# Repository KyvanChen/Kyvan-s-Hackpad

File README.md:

# Kyvan-s-Hackpad
This is my hackpad, I plan on using this for cadding in robotics. This is my first PCB and I followed hack club's tutorial sorta.

Hackpad PCB:

Hackpad Schematics:

Case:

Hackpad in case:

BOM:
- 1 XIAO RP2040
- 128x32 oled screen
- 4x Cherry MX Switches
- 4x Keycaps (3d printed?)
- 1x 3D printed Knob
- 1x 3D printed case
- 5x SK6812 mini LEDs
- 1x EC11 Rotary Encoder

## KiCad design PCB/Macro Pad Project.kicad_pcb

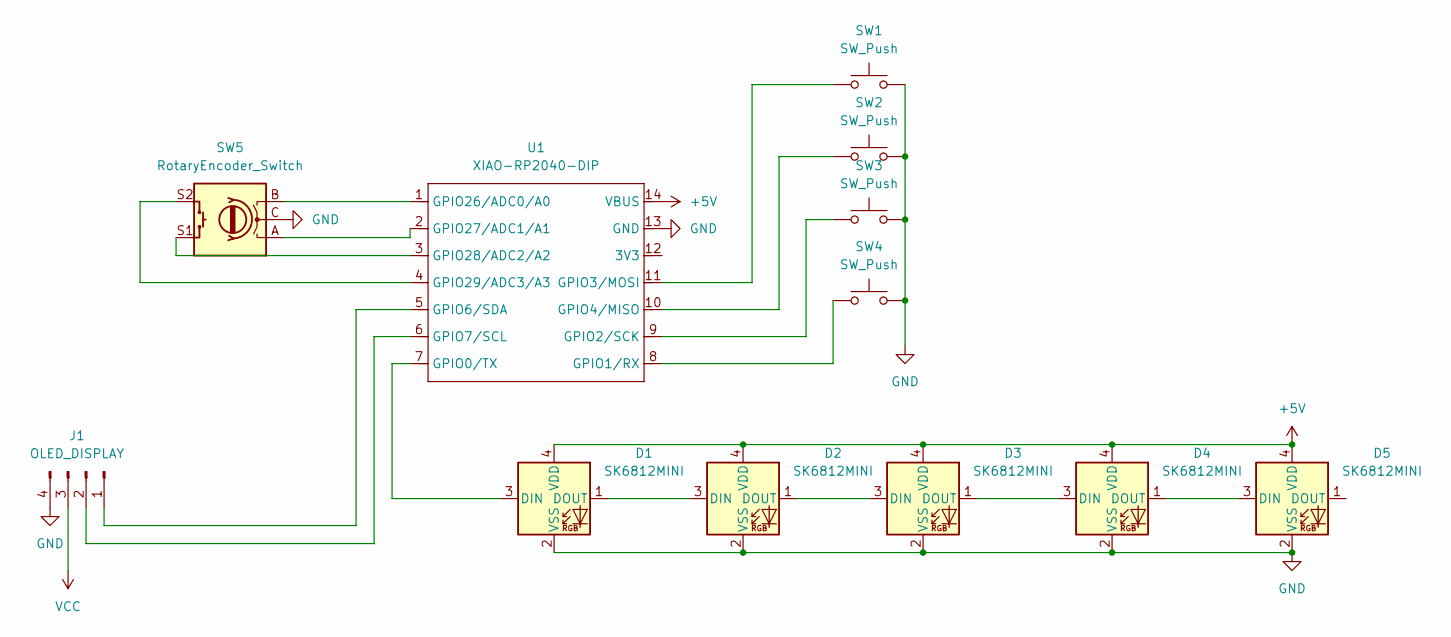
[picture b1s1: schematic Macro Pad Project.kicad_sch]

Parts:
D1, D2, D3, D4, D5: SK6812MINI; LED_SK6812MINI_PLCC4_3.5x3.5mm_P1.75mm
J1: OLED_DISPLAY; PinHeader_1x04_P2.54mm_Vertical
SW1, SW2, SW3, SW4: SW_Push; SW_Cherry_MX_1.00u_PCB
SW5: RotaryEncoder_Switch; RotaryEncoder_Alps_EC11E-Switch_Vertical_H20mm
U1: XIAO-RP2040-DIP

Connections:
+5V: D1.4 (VDD), D2.4 (VDD), D3.4 (VDD), D4.4 (VDD), D5.4 (VDD), U1.14 (VBUS)
GND: D1.2 (VSS), D2.2 (VSS), D3.2 (VSS), D4.2 (VSS), D5.2 (VSS), J1.4, SW1.2, SW2.2, SW3.2, SW4.2, SW5.C, U1.13 (GND)
unnamed: D1.3 (DIN), U1.7 (GPIO0/TX)
unnamed: D1.1 (DOUT), D2.3 (DIN)
unnamed: D2.1 (DOUT), D3.3 (DIN)
unnamed: D3.1 (DOUT), D4.3 (DIN)
unnamed: D4.1 (DOUT), D5.3 (DIN)
unnamed: J1.1, U1.5 (GPIO6/SDA)
unnamed: J1.2, U1.6 (GPIO7/SCL)
unnamed: SW4.1, U1.8 (GPIO1/RX)
unnamed: SW3.1, U1.9 (GPIO2/SCK)
unnamed: SW1.1, U1.11 (GPIO3/MOSI)
unnamed: SW2.1, U1.10 (GPIO4/MISO)
unnamed: SW5.B, U1.1 (GPIO26/ADC0/A0)
unnamed: SW5.A, U1.2 (GPIO27/ADC1/A1)
unnamed: SW5.S1, U1.3 (GPIO28/ADC2/A2)
unnamed: SW5.S2, U1.4 (GPIO29/ADC3/A3)
VCC: J1.3

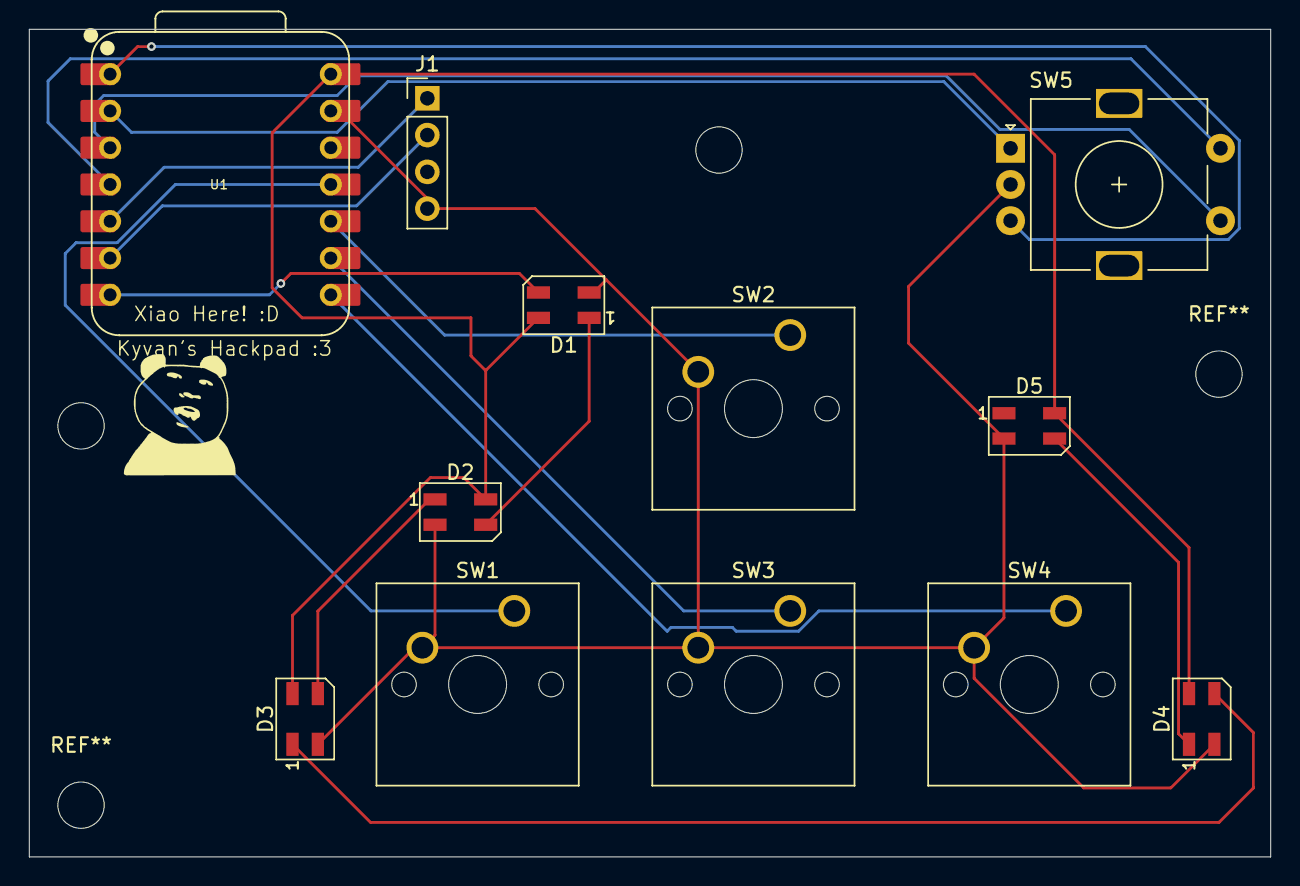
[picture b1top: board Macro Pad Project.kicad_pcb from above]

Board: 2 copper layers, 85.7 x 57.2 mm, 12 parts (0 on the bottom side), 17 nets.
